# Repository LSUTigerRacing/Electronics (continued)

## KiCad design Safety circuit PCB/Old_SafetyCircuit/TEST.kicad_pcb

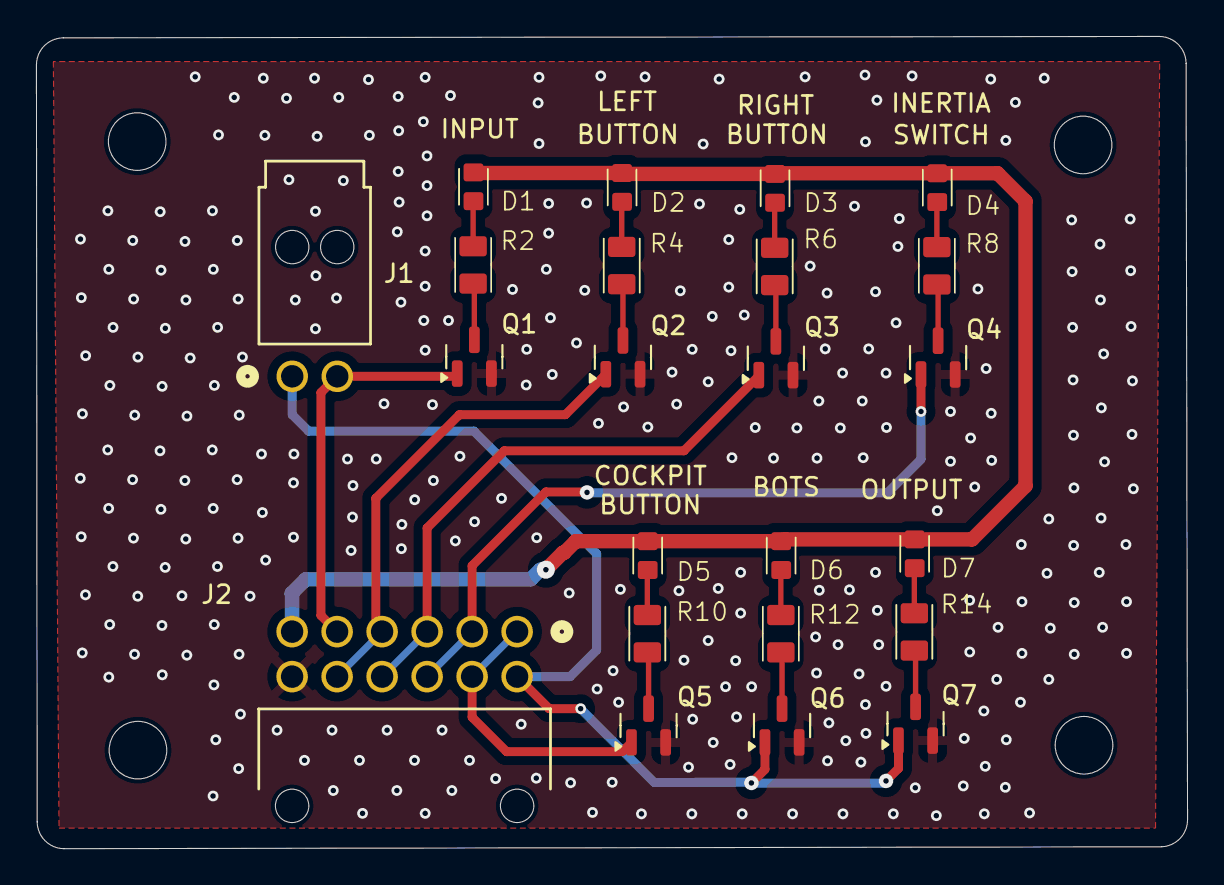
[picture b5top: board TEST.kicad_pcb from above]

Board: 2 copper layers, 63.9 x 45.1 mm, 23 parts (0 on the bottom side), 22 nets.

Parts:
D1, D2, D3, D4, D5, D6, D7: LED; HL-PSC-1608U52GC-G4
J1: 1053131202; CONN_SD-105313-100_02_MOL
J2: 1053141312; CONN_SD-105314-100_12_MOL
Q1, Q2, Q3, Q4, Q5, Q6, Q7: 2N7002K; SOT-23
R2, R4, R6, R8, R10, R12, R14: 1k; CRCW0805

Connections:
+12V: D1.2 (A), D2.2 (A), D3.2 (A), D4.2 (A), D5.2 (A), D6.2 (A), D7.2 (A), J2.6
/BOTS_END: J1.1, J2.7, Q6.1 (G), Q7.1 (G)
/BOTS_START: J2.1, J2.8, Q5.1 (G)
/COCKPIT_BUTTON_START: J2.2, J2.9, Q4.1 (G)
/INERTIA_SWITCH_START: J2.3, J2.10, Q3.1 (G)
/INPUT: J1.2, J2.5, Q1.1 (G)
/LEFT_BUTTON_END: J2.4, J2.11, Q2.1 (G)
GND: J2.12, Q1.2 (S), Q2.2 (S), Q3.2 (S), Q4.2 (S), Q5.2 (S), Q6.2 (S), Q7.2 (S)
unnamed: D1.1 (K), R2.1
unnamed: D2.1 (K), R4.1
unnamed: D3.1 (K), R6.1
unnamed: D4.1 (K), R8.1
unnamed: D5.1 (K), R10.1
unnamed: D6.1 (K), R12.1
unnamed: D7.1 (K), R14.1
unnamed: Q1.3 (D), R2.2
unnamed: Q2.3 (D), R4.2
unnamed: Q3.3 (D), R6.2
unnamed: Q4.3 (D), R8.2
unnamed: Q5.3 (D), R10.2
unnamed: Q6.3 (D), R12.2
unnamed: Q7.3 (D), R14.2
